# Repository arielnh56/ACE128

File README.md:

This library provides support for the Bourns EAW - Absolute Contacting Encoder (ACE) 

Datasheet: https://www.bourns.com/pdfs/ace.pdf

This is a small 8 bit "Gray Code" rotary position sensor providing 128 unique positions. It manages this with an [ingeniously simple mechanical design](http://redhunter.com/blog/2017/11/25/inside-the-bourns-ace-128-absolute-encoder/).

In layman's terms this is a "digital knob" you can use to control your Arduino project. It can
also be used in motion control systems with a limited lifespan.

This code is developed against the Arduino UNO R3 and Arduino MKR Wifi 1010. 

It should work on any Arduino without modification to read the sensor via my PCF8574(A) backpack modules via the I2C bus. The I2C bus must be correctly wired and include appropriate pullup resistors.

For basic testing of the manufactured modules use the ace128_0x20 and ace128_0x38 examples. These will send output to the serial monitor at 9600 baud.

See the ACE128test example sketch for detailed usage instructions for all the options.

By default the code supports **only** the PCF8574 and PCF8574A I2C expanders, as used in the author's manufactured modules, and can
optionally save state to EEPROM on AVR microcontrollers. By default it *does not save state on SAM microcontrollers* as they do
not have EEPROM - this requires a separate I2C EEPROM chip and tweaking the library to turn on support for this feature. 

The following features can be enabled via uncommenting #defines in the ACE128.h include file:
* use of MCP23008 pin expander
* use of Arduino pins to talk directly to the Bourns encoder. This disables the pin expander code. See the ace128pintest example.
* use of I2C EEPROMs to save state. These have longer life than the AVR EEPROM and provide storage for the SAM microcontrollers.
* the ability to disable the state saving code altogether and save some flash memory.

If the IDE is giving you grief editing ACE128.h then copy it to your sketch directory and use

```c++
#include "ACE128.h"
```

with quotes instead of angle brackets. That will make it use your local copy.

Installation
--------------------------------------------------------------------------------

This library conforms to the library manager standard, so it needs no special instructions here.
See https://www.arduino.cc/en/Guide/Libraries

Basic Usage
--------------------------------------------------------------------------------
See the ACE128test example sketch for more detailed instructions.

Include the library, either from the library folder with
```c++
#include <ACE128.h>
```
or copy to your sketch folder for easier editing of feature flags and use
```c++
#include "ACE128.h"
```
Note that all of the code is included in the ACE128.h file - there is no ACE128.cpp file any more. This was necessary to implement the feature flags in the Arduino IDE environment. (ask me over a beer)

* Include all the encoder maps you need (see below) to match the pin sequences of your ACE units. 
    * the manufactured modules all use the 87654321 encoder map as in the examples
* Declare all your ACE128 objects using the ACE128 constructor. It takes an I2C address and a pointer to the encoder map.
    An optional third parameter can take a positive integer to show where to store zero info in eeprom. Allow for three bytes
    for each module.
* call the begin() method for each ACE128 object from setup(). This will use the eeprom settings or fall back to setting the current position as logical zero.
* The pos() and upos() methods return the position relative to a logical zero
position rather than the zero position returned by the encoder, which is in a
mechanically arbitrary spot. When it rolls over the turns are stored for use by mpos and optionally saved in eeprom.
* Once per loop(): call pos(), upos(), or mpos() and store the value in a variable. Accessing the I2C bus takes some cycles,
so don't call pos() everytime you want to refer to it. 
* there are three setting functions
    * setZero()   - set the current location to zero (does not update multiturn)
    * setZero(int)   -  sets the zero point to the 0-127 number given
    * setMpos(int)    - sets the current location as this multiturn value. This adjust logical zero appropriately.
    * reverse(bool) - if true, makes it rising anticlockwise

Encoder Maps
--------------------------------------------------------------------------------

This library comes with various encoder maps to permit different wiring of the pins
between the ACE and the IO expander. These are useful if you are embedding the sensor in your own circuit design. The author's modules all use the 87654321 map.
Custom encoder maps are generated by the included make_encodermap example sketch as follows:
* edit the make_encodermap example sketch
* change the pinOrder array to match your wiring
* change the pinString to match your wiring
* load the sketch to the Arduino
* copy the serial monitor output to a new .h file in the ACE128 folder.  

12345678 is for the "rising counter clockwise" wiring, which matches the datasheet
numbers and is recommended for breadboard testing. 
When breadboarding, remember the pins on the sensor are numbered anticlockwise as viewed from above.

Licensing
--------------------------------------------------------------------------------

The contents of this repo are published under the MIT License. This includes the enclosed hardware designs. The project is certified as open source hardware by the Open Source Hardware Association. 

comments and feedback via https://github.com/arielnh56/ACE128

more details and videos at https://www.tindie.com/products/8759/

buy assembled units at https://redhunterstore.etsy.com/listing/1152703616/absolute-encoder-module-for-arduino

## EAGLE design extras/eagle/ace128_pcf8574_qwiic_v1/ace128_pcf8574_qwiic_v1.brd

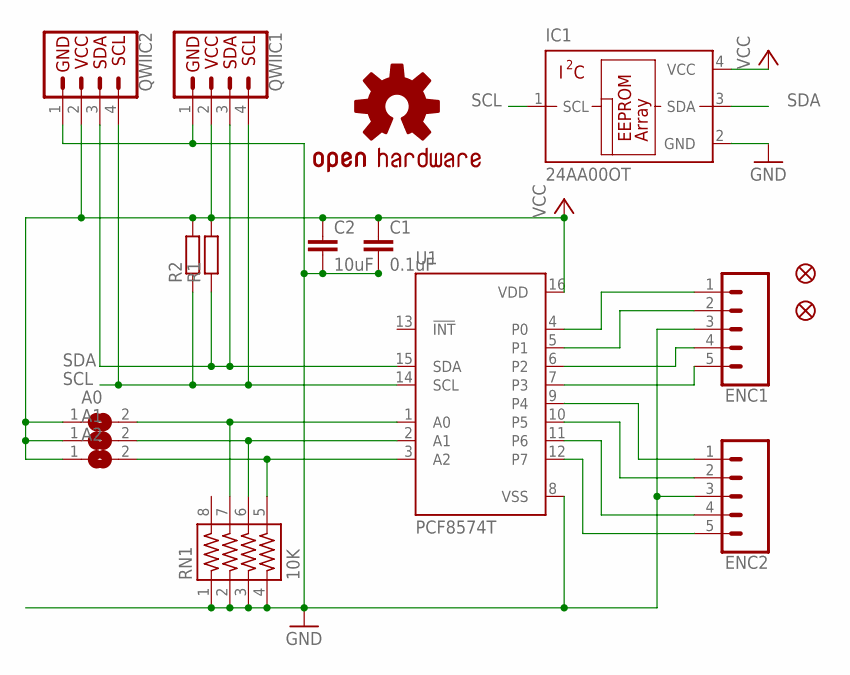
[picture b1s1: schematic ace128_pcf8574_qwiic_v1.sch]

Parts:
A0, A1, A2: SJ
C1: 0.1uF; C0603
C2: 10uF; C0805
ENC1, ENC2: CONN_05; 1X05
FD1, FD2: FIDUCIAL1X2; FIDUCIAL-1X2
IC1: 24AA00OT; SOT23-5L
LOGO1: OSHW-LOGOS; OSHW-LOGO-S
QWIIC1, QWIIC2: QWIIC_CONNECTORJS-1MM; 1X04_1MM_RA
R1, R2: R-EU_0207/2V; 0207/2V
RN1: 10K; 743-8
U1: PCF8574T; SO16W

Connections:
A0: A0.2, RN1.7, U1.1 (A0)
A1: A1.2, RN1.6, U1.2 (A1)
A2: A2.2, RN1.5, U1.3 (A2)
GND: C1.2, C2.2, ENC1.3, ENC2.3, IC1.2 (GND), QWIIC1.1 (GND), QWIIC2.1 (GND), RN1.1, RN1.2, RN1.3, RN1.4, U1.8 (VSS)
P0: ENC1.1, U1.4 (P0)
P1: ENC1.2, U1.5 (P1)
P2: ENC1.4, U1.6 (P2)
P3: ENC1.5, U1.7 (P3)
P4: ENC2.1, U1.9 (P4)
P5: ENC2.2, U1.10 (P5)
P6: ENC2.4, U1.11 (P6)
P7: ENC2.5, U1.12 (P7)
SCL: IC1.1 (SCL), QWIIC1.4 (SCL), QWIIC2.4 (SCL), R2.1, U1.14 (SCL)
SDA: IC1.3 (SDA), QWIIC1.3 (SDA), QWIIC2.3 (SDA), R1.1, U1.15 (SDA)
VCC: A0.1, A1.1, A2.1, C1.1, C2.1, IC1.4 (VCC), QWIIC1.2 (VCC), QWIIC2.2 (VCC), R1.2, R2.2, U1.16 (VDD)

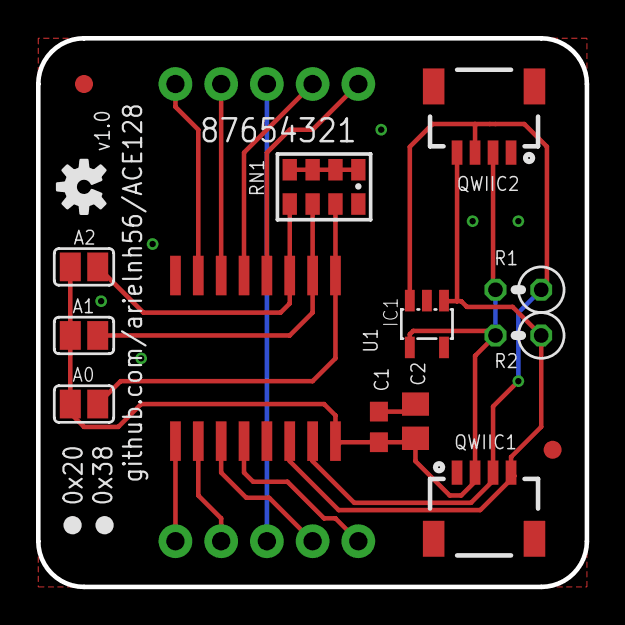
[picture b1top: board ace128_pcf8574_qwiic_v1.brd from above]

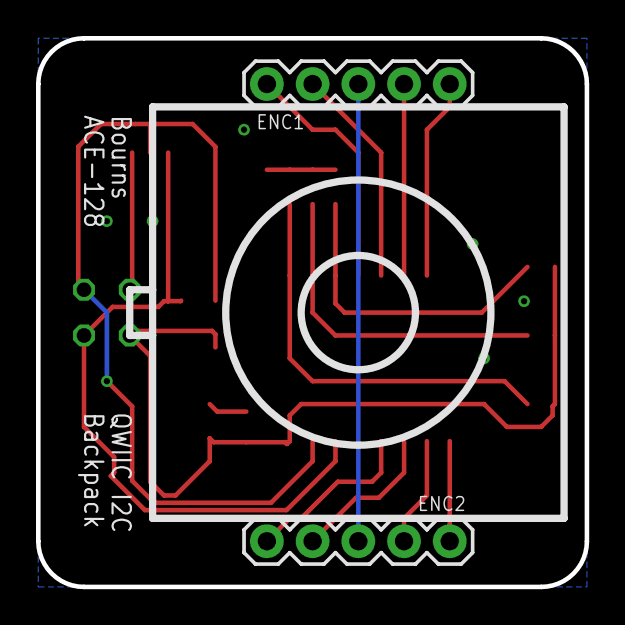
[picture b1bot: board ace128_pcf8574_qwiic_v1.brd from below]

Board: 2 copper layers, 30.5 x 30.5 mm, 17 parts (2 on the bottom side), 15 nets.

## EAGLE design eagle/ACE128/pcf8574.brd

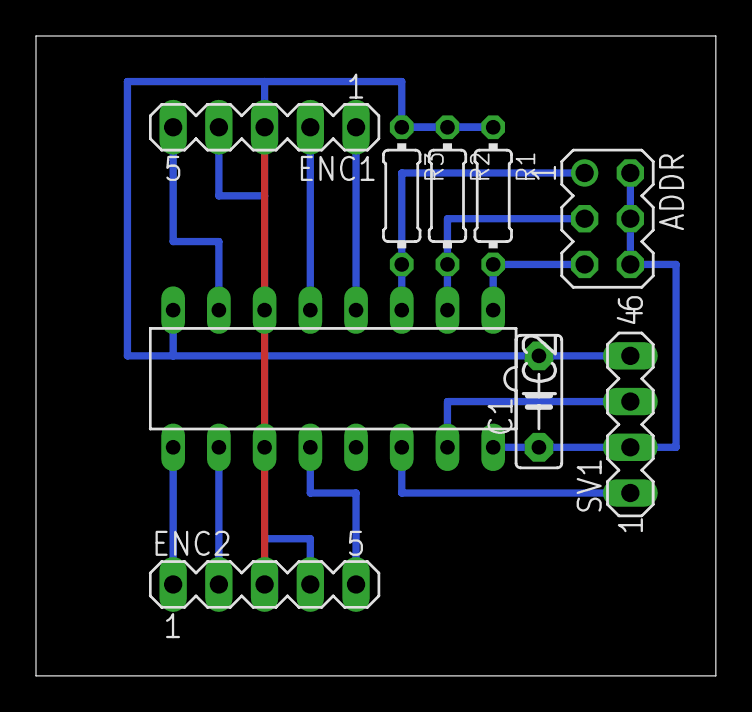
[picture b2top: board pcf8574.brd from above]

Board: 2 copper layers, 37.8 x 35.5 mm, 9 parts (0 on the bottom side), 15 nets.

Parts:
ADDR: MA03-2
C1: C5B2.5
ENC1, ENC2: MA05-1
IC2: PCF8574P; DIL16
R1, R2, R3: 0204/7
SV1: MA04-1

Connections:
unnamed: IC2.14, SV1.1
unnamed: ADDR.2, ADDR.4, ADDR.6, C1.1, IC2.16, SV1.2
unnamed: ENC2.5, IC2.12
unnamed: ADDR.5, IC2.1, R1.2
unnamed: ADDR.3, IC2.2, R2.2
unnamed: ADDR.1, IC2.3, R3.2
unnamed: IC2.15, SV1.3
unnamed: ENC2.4, IC2.11
unnamed: ENC2.2, IC2.10
unnamed: ENC2.1, IC2.9
unnamed: ENC1.4, IC2.6
unnamed: ENC1.2, IC2.5
unnamed: ENC1.1, IC2.4
unnamed: ENC1.5, IC2.7
unnamed: C1.2, ENC1.3, ENC2.3, IC2.8, R1.1, R2.1, R3.1, SV1.4

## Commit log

2013-09-02 Initial commit tp github
2015-11-01 Support for IDE 1.6 PROGMEM changes
    The syntax for PROGMEM stuff changed with IDE 1.6. This update accounts
    for this. No functional changes.
2015-11-08 Support for PCF8574
    Added support for PCF8574 and PCF8574A.
    Added MIT license.
    Removed eagle files as they were crummy and the one I actually built was
    missing..
2015-11-08 Removed reference to eagle files in readme
2017-01-16 change to library manager format
    add pin test to ACE128 test
    update readme
    add the old eagle files back in, although they are incomplete
    add fritzing file
2017-01-16 minor tweaks to docs
    fixed list in README.md
    added a picture
    added not in fritzing image that the icon for the encoder is a lie
2017-01-16 doc fix
    trying to fix the image link.
2017-01-16 tweak readme
    I wish there was a way to properly render markdown without checking in.
    dagnabbit!
2017-01-16 iterate readme
    grrr
2017-01-16 change to library manager format
    add pin test to ACE128 test
    update readme
    add the old eagle files back in, although they are incomplete
    add fritzing file
    add development flag to gitignore
    add 87654321 encoder map
2017-01-16 fix image link in readme
    markdown is driving be barmy, I tell you.
2017-02-25 Add multiturn and eeprom
    Added multiturn functions
    Added eeprom saving for zero and multiturn
    Made macros unique
    cleaned up Readme
2017-02-25 pre-release tweaks
    fix the readmie
    include the include file, missed it before
2017-03-18 Fixed test sketch
    Make sure it actually uses the I2C address macros everywhere. Duh.
2017-03-19 Fixed multiturn zero
    some positions were resulting in it being a turn off.
    cursed 7-bit binary math
2017-03-20 Multiturn zero fix
    Seems to work better this way.
2017-03-20 remove files I didn't mean to add
2017-03-26 move raw2pos calc to separate function
    this save two calls to I2C when doing setMpos()
2017-04-11 Update Eagle files
    SMD board with OSH logo. Have at it.
2017-11-17 v2.1 board
    change c1 to 0603
    add c2 10uf 0805
    route tidying
    silkscreen adds for version and address ranges.
    general silkscreen shuffle
    tented vias
2017-11-24 Silkscreen correction
    I had the C1 and C2 labels reversed.
2018-02-02 Added evaluation with 8 pins
    beside the i2c it is now possible to get the raw position with the given 8 pins. See example ace128_8Pins_test for more
2018-02-03 Adding direct pin support
    Adding support for direct pin connection.
    At this point it works on serial port.
    TODO:
    - preprocessor tags to cut out i2c code for those that want pins, and vice versa. In particular not pulling in the Wire library if not needed would save a bucket o' memory
    - testing to ensure backward compatibility
    - update the readme
2018-02-03 tidy up directpins branch
    I tried adding #defines to alternately exclude the I2C or pins code to save memory - it seemed to have no effect, so I stripped that out again.
    Updated copyrights
    fixed the #ifndef ACE28_h duh
    Updated comments
    Updated readme
    removed src.ino and put it in gitignore
2018-02-03 Version 1.7.0 Release
    Add arduino pin direct connection option.
    Two new constructors to handle this.
    Associated comments and readme updates.
2018-12-22 I2C EEPROM support
    Added support for I2C EEPROM and also for no EEPROM at all. Previous code assumes presence of EEPROM.h library which is AVR specific. Removing this requirement provides suport for non-AVR arduinies e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
    Also includes V3 board design with SOT-23-5 eeprom footprint.
2019-02-04 v3.1
    Moved the fiducials - one of them as being confused with the silkskreen version dots.
    Update version to 3.1
    Going to production with this.
2019-06-22 Combined to single .h file
    I ran into some issues getting the ifdefs to exclude unwanted code - I want to
    minimize the footprint for the AVR processors as the library starts to support more
    platforms.
    It turns out that the only way to get this to work in the normal user Arduino IDE
    environment - where people don't tweak their own compiler options - is to slam it all
    into the .h file.
2019-06-22 made MCP23008 non default
    Now enabled by #define ACE128_MCP23008
    Saves 164 bytes
2019-06-23 Separate direct pin code
    ACE128_ARDUINO_PINS now enabled the direct pin mode at *disables* I2C code,
    saving significant memory
    Major clean up of ACE128test example along with lots of commentary
    Added basic examples for manufactured modules.
2019-06-23 JUpdate Readme.md for 2.0.0 release
2019-06-23 Final tweaks for 2.0.0 release
2019-09-21 Add QWIIC Edition board v1.0
2019-10-30 Update README
    readme tweaks
2019-10-30 Update README.md
    Fun with markdown
2021-03-10 Bugfix release
    Added missing Wire.begin() in ace128test.ino
    Added caching of i2c mpos value to reduce updates
    tweaked the readme and comments
    Added QWIIC board design
2022-02-13 Create ace128_backpack_test.ino
    add backpack testing jig
2026-02-04 Update README.md
    changed link to modules to Etsy store

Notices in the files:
parts and their libraries:
SparkFun-Connectors: Licensing: Creative Commons ShareAlike 4.0 International - https://creativecommons.org/licenses/by-sa/4.0
resistor-array: Copyright (C) 2008, Bob Starr
